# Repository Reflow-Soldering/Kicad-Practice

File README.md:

<div align = "center">
  
# KiCad 연습용입니다.
### 교육이 필요하신 분은 KiCad 사이트에서 매뉴얼 참조나
### 교육사이트 이용 바랍니다

</div>

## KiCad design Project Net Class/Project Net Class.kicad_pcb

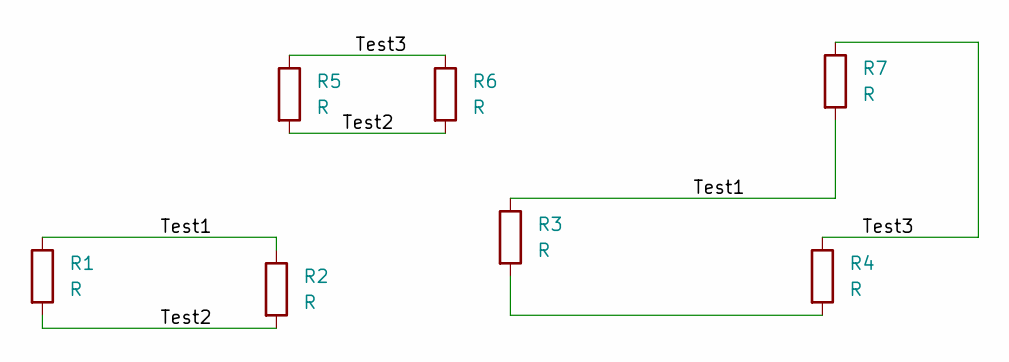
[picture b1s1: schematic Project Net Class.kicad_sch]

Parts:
R1, R2, R3, R4, R5, R6, R7: R; R_0201_0603Metric

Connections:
/Test1: R1.1, R2.1, R3.1, R7.2
/Test2: R1.2, R2.2, R5.2, R6.2
/Test3: R4.1, R5.1, R6.1, R7.1
unnamed: R3.2, R4.2

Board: 2 copper layers, 7 parts (0 on the bottom side), 4 nets, no tracks yet.

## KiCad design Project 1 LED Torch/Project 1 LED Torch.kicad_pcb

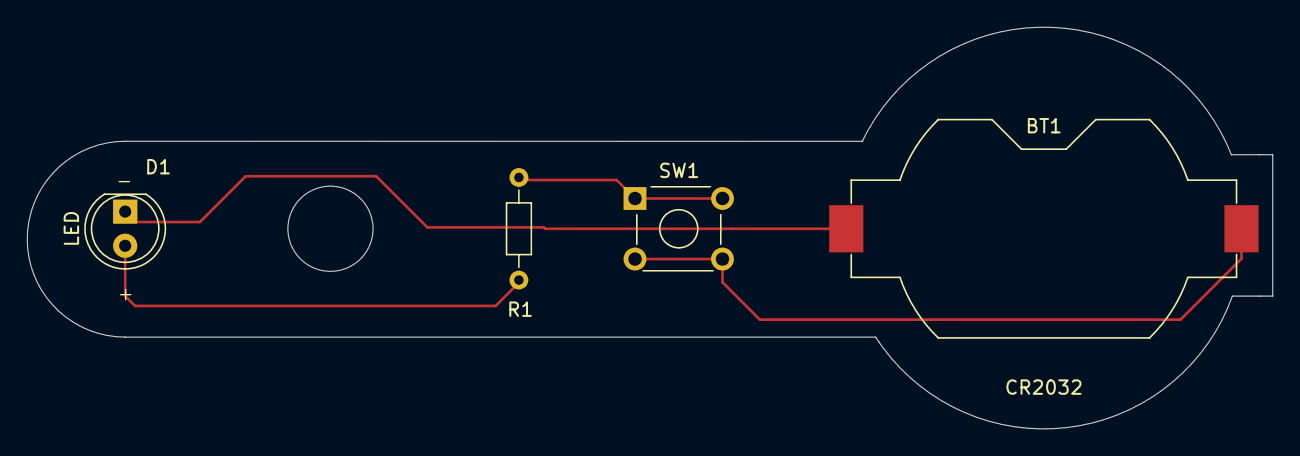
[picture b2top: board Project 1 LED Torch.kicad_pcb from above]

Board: 2 copper layers, 92.5 x 29.8 mm, 4 parts (0 on the bottom side), 4 nets.

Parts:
BT1: CR2032; BatteryHolder_Keystone_1058_1x2032
D1: LED; LED_D5.0mm
R1: R; R_Axial_DIN0204_L3.6mm_D1.6mm_P7.62mm_Horizontal
SW1: SW_DPDT_x2; SW_TH_Tactile_Omron_B3F-10xx

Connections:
/BAT_Pos: BT1.1 (+), SW1.2 (B)
/LED_Anode: D1.2 (A), R1.1
/LED_Cathode: BT1.2 (-), D1.1 (K)
unnamed: R1.2, SW1.1 (A)

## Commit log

2025-07-01 LED Torch 관련 커밋
    따라 그리기 진행 완료
2025-07-01 Net Class 관련 내용
    이놈은 계속 변경 예정
2025-07-01 계층 구조 테스트
    계층 구조 테스트
    실제 PCB는 언제 짜볼라나
2025-07-01 망했다
    뭐가 빠졌을라나
